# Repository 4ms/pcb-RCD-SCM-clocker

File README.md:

# PCB for RCD and SCM eurorack modules #

## Rotating Clock Divider, and Shuffling Clock Multiplier ##

### Pre-built versions (PCB v1.2) and Kit version (PCB v1.0.x) ###

This repository is an archive for the kit and pre-built versions of the RCD and SCM.

While we believe these files are accurate, there may be minor variations and/or corrections made during assembly that aren't recorded in these files.

Copyright (c) 2010, 2011, 2014, 2020 Dan Green (danngreen1@gmail.com)

Licensed by the [CC BY-NC-SA license](https://creativecommons.org/licenses/by-nc-sa/4.0/) (Creative Commons, Attribution, NonCommercial, ShareAlike).

Please read the above license carefully and contact us if you have any questions regarding acceptable use of these files.

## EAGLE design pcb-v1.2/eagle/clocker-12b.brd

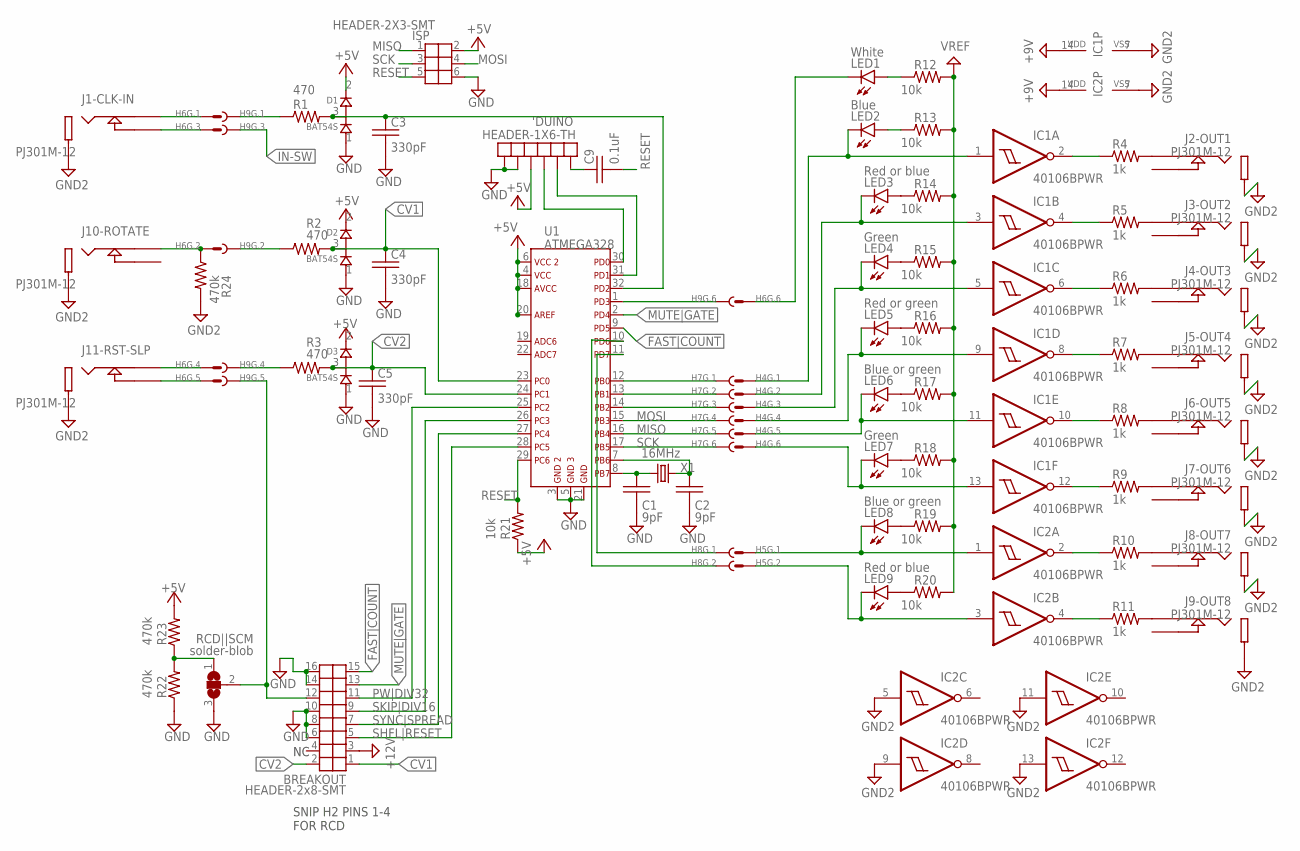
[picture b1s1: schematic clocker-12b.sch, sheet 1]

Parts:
'DUINO: HEADER-1X6-TH
BREAKOUT: HEADER-2x8-SMT; HEADER-2X8-SMT
C1, C2: 9pF; C0603
C3, C4, C5: 330pF; C0603
C9: 0.1uF; C0603
D1, D2, D3: BAT54S; SOT23
H4, H5, H6: HEADER-2X3-B2B-MALESMT; HEADER-2X3-SMT
H7, H8, H9: HEADER-2X3-B2B-FEMALETH-BOT; HEADER-2X3-TH-BOTTOM
IC1, IC2: 40106BPWR; TSSOP14
ISP: HEADER-2X3-SMT
J1-CLK-IN, J2-OUT1, J3-OUT2, J4-OUT3, J5-OUT4, J6-OUT5, J7-OUT6, J8-OUT7, J9-OUT8, J10-ROTATE, J11-RST-SLP: PJ301M-12
LED1: White; LED-T1
LED2: Blue; LED-T1
LED3, LED9: Red or blue; LED-T1
LED4, LED7: Green; LED-T1
LED5: Red or green; LED-T1
LED6, LED8: Blue or green; LED-T1
R1, R2, R3: 470; R0603
R4, R5, R6, R7, R8, R9, R10, R11: 1k; R0603
R12, R13, R14, R15, R16, R17, R18, R19, R20, R21: 10k; R0603
R22, R23, R24: 470k; R0603
RCD||SCM: solder-blob; SJ_2
U1: ATMEGA328; TQFP-32
X1: 16MHz; FA-238

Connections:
+5V: 'DUINO.P$3, D1.2 (CATHODE), D2.2 (CATHODE), D3.2 (CATHODE), ISP.2, R21.1, R23.2, U1.4, U1.6, U1.18, U1.20; also elsewhere on the board
+9V: IC1.14 (VDD), IC2.14 (VDD); also elsewhere on the board
+12V: BREAKOUT.3; also elsewhere on the board
+VREF: R12.2, R13.2, R14.2, R15.2, R16.2, R17.2, R18.2, R19.2, R20.2; also elsewhere on the board
AGND: IC1.7 (VSS), IC2.5 (I), IC2.7 (VSS), IC2.9 (I), IC2.11 (I), IC2.13 (I), J1-CLK-IN.2 (SLEEVE), J2-OUT1.2 (SLEEVE), J3-OUT2.2 (SLEEVE), J4-OUT3.2 (SLEEVE), J5-OUT4.2 (SLEEVE), J6-OUT5.2 (SLEEVE), J7-OUT6.2 (SLEEVE), J8-OUT7.2 (SLEEVE), J9-OUT8.2 (SLEEVE), J10-ROTATE.2 (SLEEVE), J11-RST-SLP.2 (SLEEVE), R24.2; also elsewhere on the board
CV1: BREAKOUT.1, C4.1, D2.3 (COMMON), R2.2, U1.23
CV2: BREAKOUT.2, C5.1, D3.3 (COMMON), R3.2, U1.24
CV2-SW: BREAKOUT.12, H9.P$5, RCD||SCM.2
FAST|COUNT: BREAKOUT.15, U1.9
GND: 'DUINO.P$1, 'DUINO.P$2, BREAKOUT.6, BREAKOUT.8, BREAKOUT.10, BREAKOUT.14, BREAKOUT.16, C1.2, C2.2, C3.2, C4.2, C5.2, D1.1 (ANODE), D2.1 (ANODE), D3.1 (ANODE), ISP.6, R22.1, RCD||SCM.3, U1.3, U1.5, U1.21; also elsewhere on the board
IN-SW: H9.P$3; also elsewhere on the board
INLED: H6.6, LED1.K (C)
MISO: H7.P$5, ISP.1, U1.16
MOSI: H7.P$4, ISP.4, U1.15
MUTE|GATE: BREAKOUT.13, U1.2
unnamed: C1.1, U1.8, X1.3 (2)
unnamed: C2.1, U1.7, X1.1
unnamed: J2-OUT1.1 (TIP), R4.2
unnamed: J3-OUT2.1 (TIP), R5.2
unnamed: J4-OUT3.1 (TIP), R6.2
unnamed: J5-OUT4.1 (TIP), R7.2
unnamed: J6-OUT5.1 (TIP), R8.2
unnamed: J7-OUT6.1 (TIP), R9.2
unnamed: J8-OUT7.1 (TIP), R10.2
unnamed: J9-OUT8.1 (TIP), R11.2
unnamed: C3.1, D1.3 (COMMON), R1.2, U1.32
unnamed: LED4.A, R15.1
unnamed: LED5.A, R16.1
unnamed: H6.1, J1-CLK-IN.1 (TIP)
unnamed: H9.P$4, R3.1
unnamed: H9.P$2, R2.1
unnamed: LED1.A, R12.1
unnamed: LED6.A, R17.1
unnamed: 'DUINO.P$4, U1.30
unnamed: LED2.A, R13.1
unnamed: LED3.A, R14.1
unnamed: LED7.A, R18.1
unnamed: LED8.A, R19.1
unnamed: LED9.A, R20.1
unnamed: R22.2, R23.1, RCD||SCM.1
unnamed: H8.P$1, U1.11
unnamed: H9.P$6, U1.1
unnamed: H8.P$2, U1.10
unnamed: H7.P$1, U1.12
unnamed: 'DUINO.P$5, U1.31
unnamed: 'DUINO.P$6, C9.1
unnamed: H6.3, J1-CLK-IN.3 (TIP-SW)
unnamed: H6.2, J10-ROTATE.1 (TIP), R24.1
unnamed: H6.4, J11-RST-SLP.1 (TIP)
unnamed: IC2.4 (O), R11.1
unnamed: IC1.2 (O), R4.1
unnamed: IC1.4 (O), R5.1
unnamed: IC1.6 (O), R6.1
unnamed: IC1.8 (O), R7.1
unnamed: IC1.10 (O), R8.1
unnamed: IC1.12 (O), R9.1
unnamed: IC2.2 (O), R10.1
unnamed: H6.5, J11-RST-SLP.3 (TIP-SW)
unnamed: H7.P$3, U1.14
unnamed: H7.P$2, U1.13
unnamed: H9.P$1, R1.1
OUTLINE1: H4.1, IC1.1 (I), LED2.K (C)
OUTLINE2: H4.2, IC1.3 (I), LED3.K (C)
OUTLINE3: H4.3, IC1.5 (I), LED4.K (C)
OUTLINE4: H4.4, IC1.9 (I), LED5.K (C)
OUTLINE5: H4.5, IC1.11 (I), LED6.K (C)
OUTLINE6: H4.6, IC1.13 (I), LED7.K (C)
OUTLINE7: H5.1, IC2.1 (I), LED8.K (C)
OUTLINE8: H5.2, IC2.3 (I), LED9.K (C)
PW|DIV32: BREAKOUT.11, U1.25
RESET: C9.2, ISP.5, R21.2, U1.29
SCK: H7.P$6, ISP.3, U1.17
SHFL|RESET: BREAKOUT.5, U1.28
SKIP|DIV16: BREAKOUT.9, U1.26
SYNC|SPREAD: BREAKOUT.7, U1.27

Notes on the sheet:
SNIP H2 PINS 1-4 FOR RCD

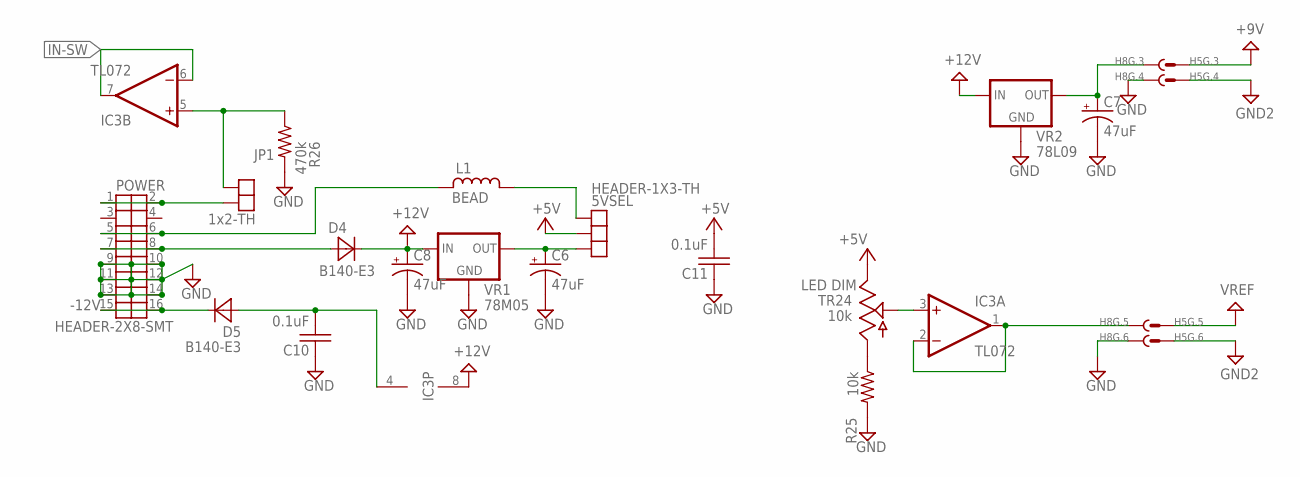
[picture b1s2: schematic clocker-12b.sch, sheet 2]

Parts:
5VSEL: HEADER-1X3-TH
C6, C7, C8: 47uF; C-POL-5
C10, C11: 0.1uF; C0603
D4, D5: B140-E3; SMA
H5: HEADER-2X3-B2B-MALESMT; HEADER-2X3-SMT
H8: HEADER-2X3-B2B-FEMALETH-BOT; HEADER-2X3-TH-BOTTOM
IC3: TL072; SOIC8
JP1: 1x2-TH; HEADER-1X2-TH
L1: BEAD; 0603
POWER: HEADER-2X8-SMT; HEADER-2X8-SMT-SHROUDED
R25: 10k; R0603
R26: 470k; R0603
TR24: 10k; PIHER-6MM
VR1: 78M05; DPAK
VR2: 78L09; SOT89

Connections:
+5V: 5VSEL.P$2, C11.2, TR24.3; also elsewhere on the board
+9V: H5.3; also elsewhere on the board
+12V: C8.+, D4.K (C), IC3.8 (V+), VR1.1 (IN), VR2.3 (IN); also elsewhere on the board
+VREF: H5.5; also elsewhere on the board
-12V: D5.K (C), POWER.15, POWER.16
AGND: H5.4, H5.6; also elsewhere on the board
GND: C6.-, C7.-, C8.-, C10.1, C11.1, H8.P$4, H8.P$6, POWER.9, POWER.10, POWER.11, POWER.12, POWER.13, POWER.14, R25.2, R26.2, VR1.4 (GND), VR2.2A (GND), VR2.2B (GND); also elsewhere on the board
IN-SW: IC3.6 (-IN), IC3.7 (OUT); also elsewhere on the board
unnamed: IC3.5 (+IN), JP1.P$1, R26.1
unnamed: C10.2, D5.A, IC3.4 (V-)
unnamed: JP1.P$2, POWER.1, POWER.2
unnamed: L1.1, POWER.5, POWER.6
unnamed: D4.A, POWER.7, POWER.8
unnamed: C7.+, H8.P$3, VR2.1 (OUT)
unnamed: 5VSEL.P$3, C6.+, VR1.3 (OUT)
unnamed: 5VSEL.P$1, L1.2 (4)
unnamed: H8.P$5, IC3.1 (OUT), IC3.2 (-IN)
unnamed: IC3.3 (+IN), TR24.2
unnamed: R25.1, TR24.1

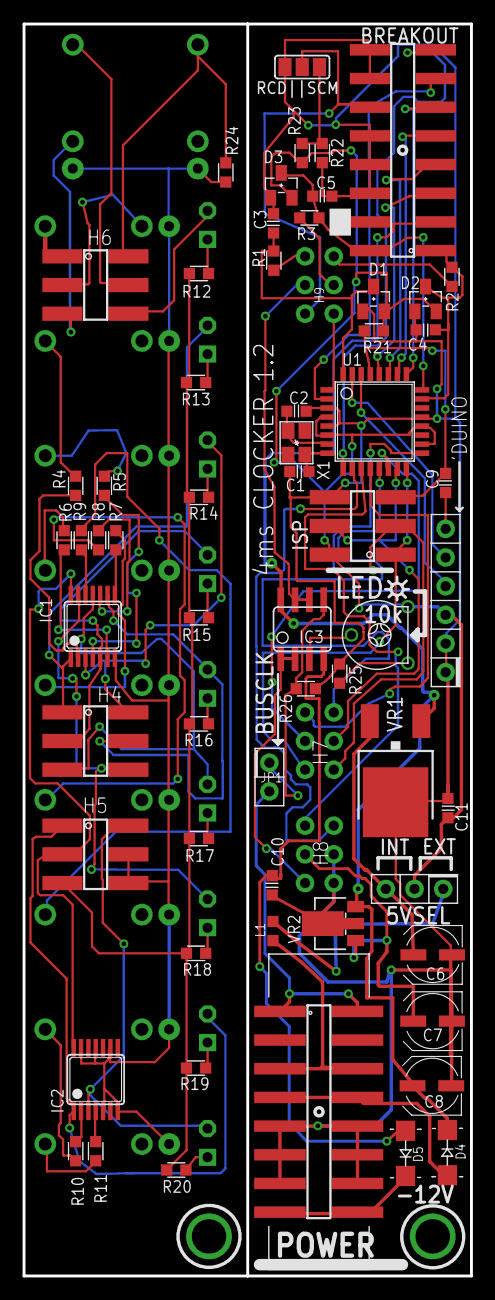
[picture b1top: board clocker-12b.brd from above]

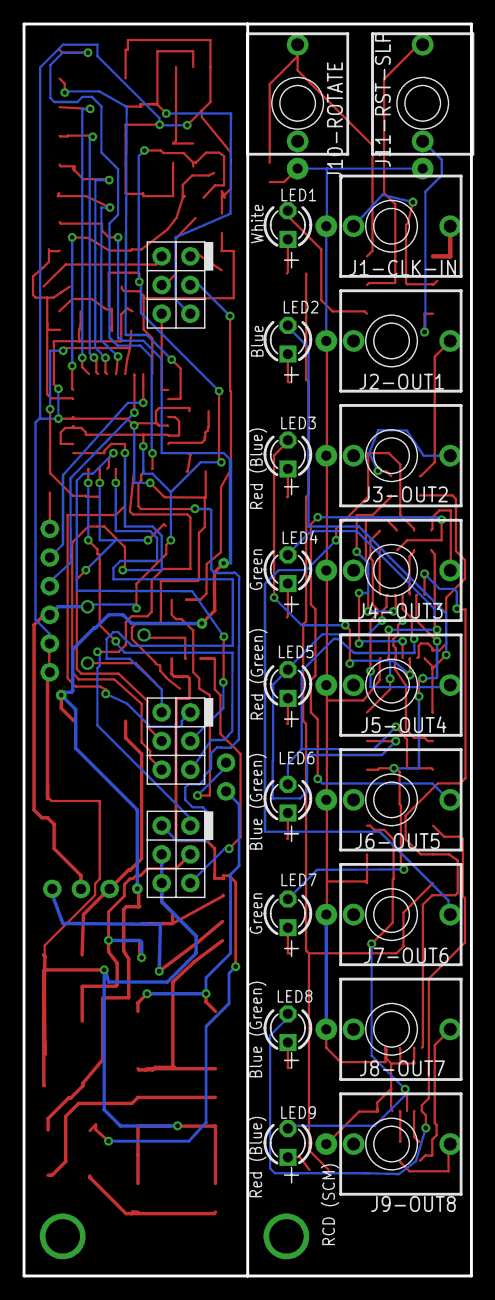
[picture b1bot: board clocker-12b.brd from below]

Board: 2 copper layers, 39.6 x 110.9 mm, 84 parts (20 on the bottom side), 87 nets.

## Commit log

2020-09-07 Added PCB v1.2 Eagle and Kicad projects; PCB 1.0.4d gEDA project
2020-09-07 Added README
